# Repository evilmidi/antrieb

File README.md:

# antrieb 
> sequencer made for live</center>

# Features (done)
- 16 channels
- 128 steps
- 32 step buttons on 4 pages
-  8 CC values on each step
-  8 encoder 

- Teensy 3.6 powered
- Midi In and Out
- USB Midi Host for external midi devices
- OLED Display 128 x 64  

- Micro SD Slot
- USB Powered

# Features (IM WORKING ON)
- cv out
- Save and load from sd card
- multiple patterns

​
# key mapping

> There are a lot of combination. In general, every combination takes the function of both and creates a new meaning. So it should be easy to find and remember them.

# Overview
<kbd>F</kbd> <kbd>1..8</kbd> controls the value displayed opn the display under it

<section>
<kbd>S </kbd><kbd>1..32</kbd>
+ **press**  sets activate a step

+ **release**  deactivetes the step if it was active

+ **hold** for 600ms:  the display will just show the step parameters on release

</section>
<kbd>I</kbd> <kbd>1..16</kbd> select an instrument. second press playes the default note

<kbd>I</kbd>+<kbd>F</kbd>

## Playback
<kbd>play</kbd> starts and pauses the playback
<kbd>shift</kbd>+ <kbd>play</kbd> starts from the beginning and sets all pattern to the first step

## Recording
<kbd>rec</kbd> starts and stops the recording

## Patterns
<kbd>shift</kbd> + <kbd>I</kbd> changes the running pattern of the selected instrument
<kbd>play</kbd> + <kbd>I</kbd> changes the running pattern for all instruments

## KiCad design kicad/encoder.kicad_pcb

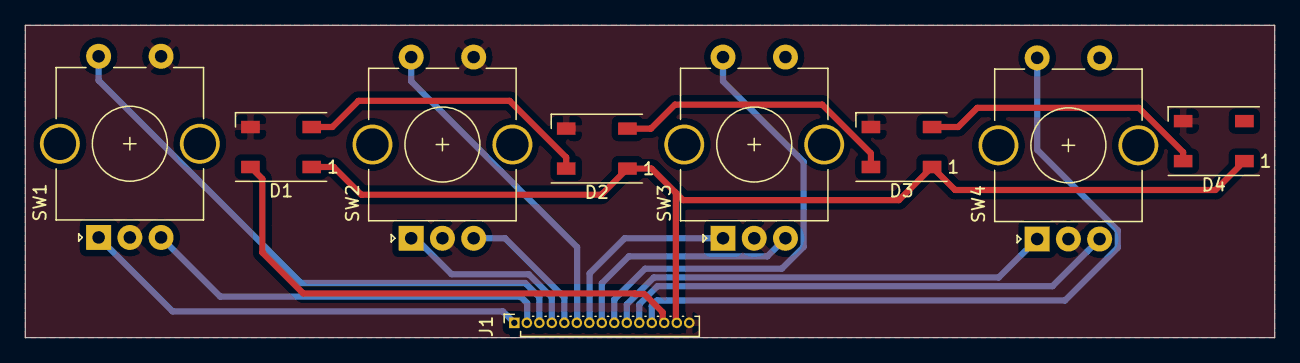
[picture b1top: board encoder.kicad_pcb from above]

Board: 2 copper layers, 100.0 x 25.0 mm, 9 parts (0 on the bottom side), 18 nets.

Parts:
D1, D2, D3, D4: WS2812B; LED_WS2812B_PLCC4_5.0x5.0mm_P3.2mm
J1: Conn_01x15; PinSocket_1x15_P1.00mm_Vertical
SW1, SW2, SW3, SW4: Rotary_Encoder_Switch; RotaryEncoder_Alps_EC11E-Switch_Vertical_H20mm_CircularMoun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

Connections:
5v: D1.1, D2.1, D3.1, D4.1, J1.14
unnamed: D1.2, D2.4
unnamed: D2.2, D3.4
unnamed: D3.2, D4.4
unnamed: J1.1, SW1.A
unnamed: J1.2, SW1.B
unnamed: J1.3, SW1.S2
unnamed: J1.4, SW2.A
unnamed: J1.5, SW2.B
unnamed: J1.6, SW2.S2
unnamed: J1.7, SW3.A
unnamed: J1.8, SW3.B
unnamed: J1.9, SW3.S2
unnamed: J1.10, SW4.A
unnamed: J1.11, SW4.B
unnamed: J1.12, SW4.S2
data: D1.4, J1.13
gnd: D1.3, D2.3, D3.3, D4.3, J1.15, SW1.C, SW1.S1, SW2.C, SW2.S1, SW3.C, SW4.C

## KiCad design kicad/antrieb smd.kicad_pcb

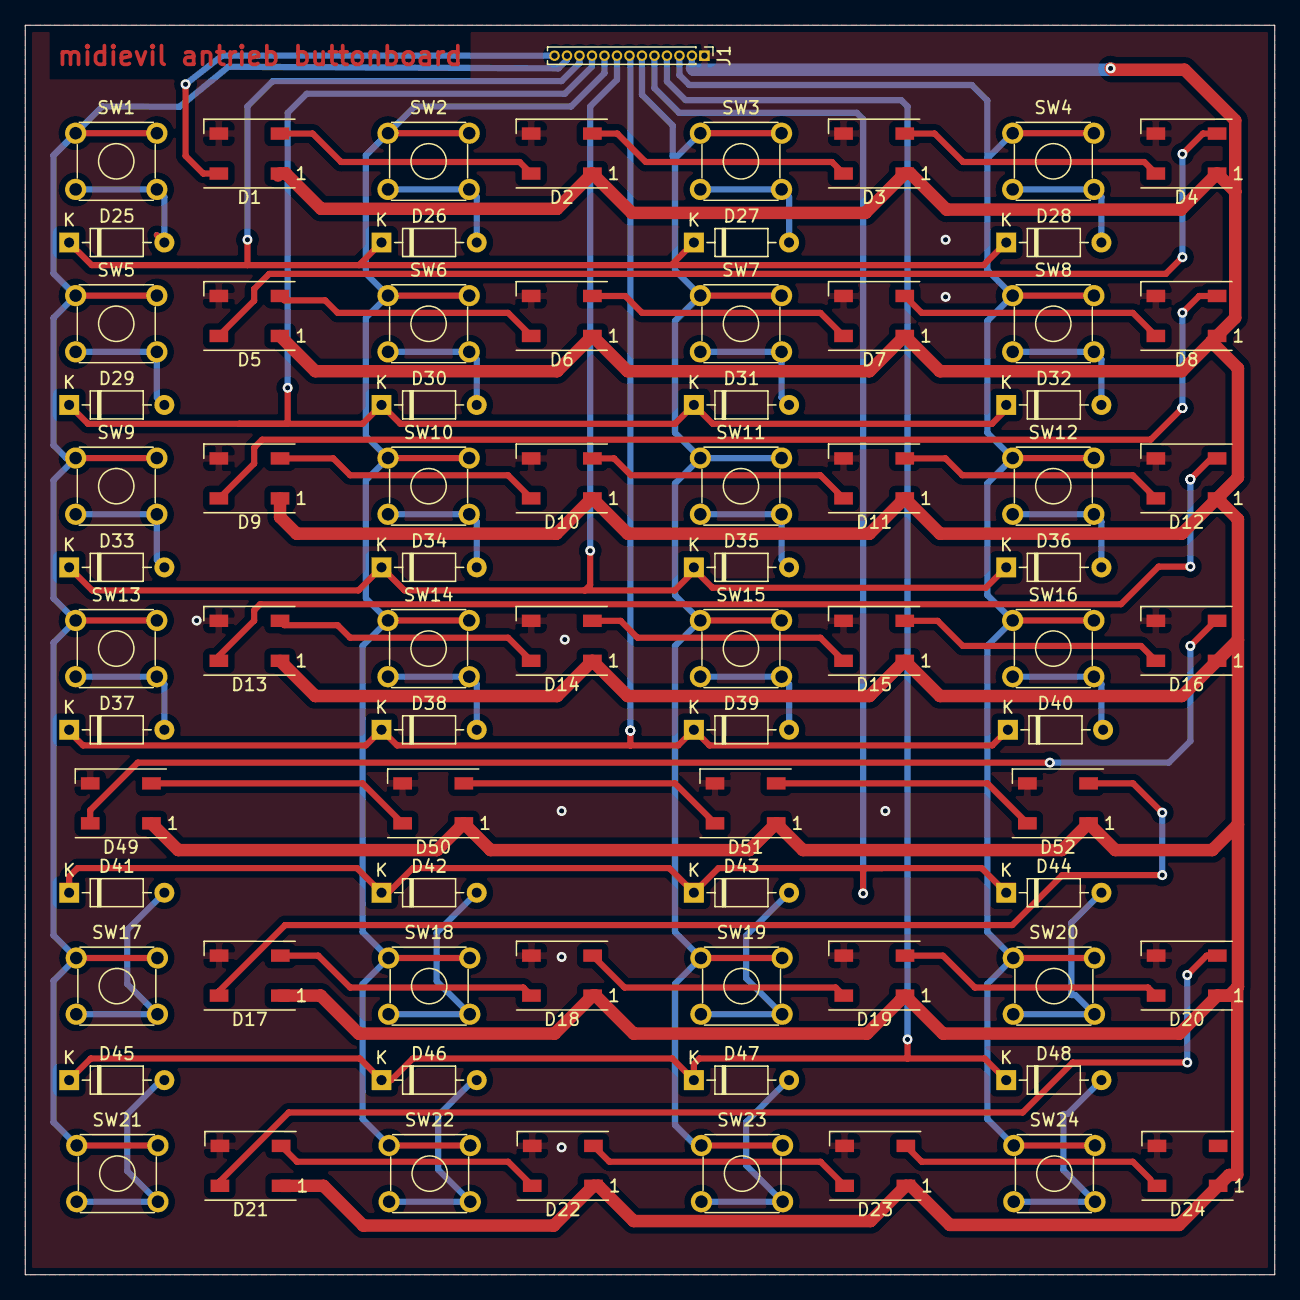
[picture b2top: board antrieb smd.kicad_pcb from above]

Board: 2 copper layers, 100.0 x 100.0 mm, 77 parts (0 on the bottom side), 64 nets.

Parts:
D1, D2, D3, D4, D5, D6, D7, D8, D9, D10, D11, D12, D13, D14, D15, D16, D17, D18, D19, D20, D21, D22, D23, D24, D49, D50, D51, D52: WS2812B; LED_WS2812B_PLCC4_5.0x5.0mm_P3.2mm
D25, D26, D27, D28, D29, D30, D31, D32, D33, D34, D35, D36, D37, D38, D39, D40, D41, D42, D43, D44, D45, D46, D47, D48: 1N4001; D_DO-35_SOD27_P7.62mm_Horizontal
J1: Conn_01x13_Male; PinHeader_1x13_P1.00mm_Vertical
SW1, SW2, SW3, SW4, SW5, SW6, SW7, SW8, SW9, SW10, SW11, SW12, SW13, SW14, SW15, SW16, SW17, SW18, SW19, SW20, SW21, SW22, SW23, SW24: SW_MEC_5G; SW_TH_Tactile_Omron_B3F-10xx

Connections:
5v: D1.1, D2.1, D3.1, D4.1, D5.1, D6.1, D7.1, D8.1, D9.1, D10.1, D11.1, D12.1, D13.1, D14.1, D15.1, D16.1, D17.1, D18.1, D19.1, D20.1, D21.1, D22.1, D23.1, D24.1, D49.1, D50.1, D51.1, D52.1, J1.2
unnamed: D1.2, D2.4
unnamed: D2.2, D3.4
unnamed: D3.2, D4.4
unnamed: D4.2, D5.4
unnamed: D5.2, D6.4
unnamed: D6.2, D7.4
unnamed: D7.2, D8.4
unnamed: D8.2, D9.4
unnamed: D10.2, D11.4
unnamed: D9.2, D10.4
unnamed: D11.2, D12.4
unnamed: D12.2, D13.4
unnamed: D13.2, D14.4
unnamed: D14.2, D15.4
unnamed: D15.2, D16.4
unnamed: D16.2, D49.4
unnamed: D17.2, D18.4
unnamed: D17.4, D52.2
unnamed: D18.2, D19.4
unnamed: D19.2, D20.4
unnamed: D20.2, D21.4
unnamed: D21.2, D22.4
unnamed: D22.2, D23.4
unnamed: D23.2, D24.4
unnamed: D25.2, SW1.3, SW1.4
unnamed: D26.2, SW2.3, SW2.4
unnamed: D27.2, SW3.3, SW3.4
unnamed: D28.2, SW4.3, SW4.4
unnamed: D29.2, SW5.3, SW5.4
unnamed: D30.2, SW6.3, SW6.4
unnamed: D31.2, SW7.3, SW7.4
unnamed: D32.2, SW8.3, SW8.4
unnamed: D33.2, SW9.3, SW9.4
unnamed: D34.2, SW10.3, SW10.4
unnamed: D35.2, SW11.3, SW11.4
unnamed: D36.2, SW12.3, SW12.4
unnamed: D37.2, SW13.3, SW13.4
unnamed: D38.2, SW14.3, SW14.4
unnamed: D39.2, SW15.3, SW15.4
unnamed: D40.2, SW16.3, SW16.4
unnamed: D41.2, SW17.3, SW17.4
unnamed: D42.2, SW18.3, SW18.4
unnamed: D43.2, SW19.3, SW19.4
unnamed: D44.2, SW20.3, SW20.4
unnamed: D45.2, SW21.3, SW21.4
unnamed: D46.2, SW22.3, SW22.4
unnamed: D47.2, SW23.3, SW23.4
unnamed: D48.2, SW24.3, SW24.4
unnamed: D49.2, D50.4
unnamed: D50.2, D51.4
unnamed: D51.2, D52.4
col1: J1.12, SW1.1, SW1.2, SW5.1, SW5.2, SW9.1, SW9.2, SW13.1, SW13.2, SW17.1, SW17.2, SW21.1, SW21.2
col2: J1.9, SW2.1, SW2.2, SW6.1, SW6.2, SW10.1, SW10.2, SW14.1, SW14.2, SW18.1, SW18.2, SW22.1, SW22.2
col3: J1.6, SW3.1, SW3.2, SW7.1, SW7.2, SW11.1, SW11.2, SW15.1, SW15.2, SW19.1, SW19.2, SW23.1, SW23.2
col4: J1.3, SW4.1, SW4.2, SW8.1, SW8.2, SW12.1, SW12.2, SW16.1, SW16.2, SW20.1, SW20.2, SW24.1, SW24.2
data: D1.4, J1.13
gnd: D1.3, D2.3, D3.3, D4.3, D5.3, D6.3, D7.3, D8.3, D9.3, D10.3, D11.3, D12.3, D13.3, D14.3, D15.3, D16.3, D17.3, D18.3, D19.3, D20.3, D21.3, D22.3, D23.3, D24.3, D49.3, D50.3, D51.3, D52.3, J1.1
row1: D25.1, D26.1, D27.1, D28.1, J1.11
row2: D29.1, D30.1, D31.1, D32.1, J1.10
row3: D33.1, D34.1, D35.1, D36.1, J1.8
row4: D37.1, D38.1, D39.1, D40.1, J1.7
row5: D41.1, D42.1, D43.1, D44.1, J1.5
row6: D45.1, D46.1, D47.1, D48.1, J1.4

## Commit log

2020-06-18 add image
2020-06-18 add rendered image
